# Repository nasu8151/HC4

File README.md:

¡¡¡ガバガバEnglish注意報発令中!!!

# Table of Contents
- [Table of Contents](#table-of-contents)
- [Descriptions](#descriptions)
- [Architecture](#architecture)
  - [Overview](#overview)
  - [Block diagram](#block-diagram)
  - [Instructions list](#instructions-list)
- [Software](#software)
- [List of files and folders](#list-of-files-and-folders)

# Descriptions

A 4- or 8-bit CPU made with 74-series logic ICs.

# Manuals

- Hardware manual (JP): [UsersManual_Hardware.md](./UsersManual_Hardware.md)
- Software manual (EN): [UsersManual_Software.md](./UsersManual_Software.md)
- Software manual (JP): [UsersManual_Software_JP.md](./UsersManual_Software_JP.md)

Document roles:

- Hardware manual (JP): block-level architecture, buses, control signals, model differences.
- Software manual (EN/JP): instruction set reference, programming caveats, and LED blink tutorial.

# Architecture
## Overview

HC4 has an 8-bit wide address bus and a 4-bit wide data bus.
All of instructions are 8-bit wide.

## Block diagram

## Instructions list

Please refer to [here](https://github.com/nasu8151/HC4/blob/main/UsersManual_Software.md).

## Schematics and Boards

If you don't have [KiCAD](https://www.kicad.org/), you can use KiCanvas to see our schematics and boards.
* [HC4](https://kicanvas.org/?repo=https%3A%2F%2Fgithub.com%2Fnasu8151%2FHC4%2Ftree%2Fmain%2FHC4_KiCad)
* [HC4<sub>E</sub>](https://kicanvas.org/?repo=https%3A%2F%2Fgithub.com%2Fnasu8151%2FHC4%2Ftree%2Fmain%2FHC4_KiCad_EE)

# Software

## Assembler

The assembler for this CPU can be found [here](https://github.com/nasu8151/hcxasm).
Please see the documents for syntax and other details.

## HC4eROMandRAM

This is a ROM/RAM emulator for HC4<sub>E</sub>.

# List of files and folders

<pre>
.
├─extra
├─HC4eROMandRAM
│  └─inst
├─hc4_asm
│  └─src
│      └─debug_data
├─HC4_KiCad
│  ├─HC4_gbr
│  ├─Library.pretty
│  └─sim
├─HC4_KiCad_EE
│  ├─HC4_KiCad_EE-backups
│  ├─Library.pretty
│  └─production
├─HC_MemoryBoard
│  ├─production
│  └─ThroughHole.pretty
└─verilog
    ├─HC4
    ├─HC4e
    └─HC8
</pre>

* [README.md](https://github.com/nasu8151/HC4) : This file.
* [UsersManual_Software.md](https://github.com/nasu8151/HC4/blob/main/UsersManual_Software.md) : Instruction manual.
* [hc4_asm/](https://github.com/nasu8151/HC4/blob/main/hc4_asm) : [DEPRECATED] : [Use new assembler](https://github.com/nasu8151/hcxasm). An assembler for the HC4 CPU.
* [HC4_KiCad](https://github.com/nasu8151/HC4/blob/main/HC4_KiCad) : Schematics and a board of the HC4.
* [HC4_KiCad_EE](https://github.com/nasu8151/HC4/blob/main/HC4_KiCad_EE) : Schematics and a board of the HC4<sub>E</sub> (Used to be called "HC4 Education Edition").
* [HC_MemoryBoard](https://github.com/nasu8151/HC4/blob/main/HC4_KiCad_EE) : A schematic and a board for SRAM and I/O.
* verilog/
  * [verilog/HC4](https://github.com/nasu8151/HC4/blob/main/verilog/HC4) : Verilog simulation files of the HC4 CPU.
  * [verilog/HC8](https://github.com/nasu8151/blob/main/HC4/verilog/HC8) : Verilog simulation files of the HC8 CPU.
  * [verilog/HC4e](https://github.com/nasu8151/blob/main/HC4/verilog/HC8) : Verilog simulation files of the HC4e CPU.

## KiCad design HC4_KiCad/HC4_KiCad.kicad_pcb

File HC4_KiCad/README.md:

Schematics and board of HC4.

BOM:
[Bill of materials](https://github.com/nasu8151/HC4/blob/main/HC4_KiCad/BOM_HC4.md)

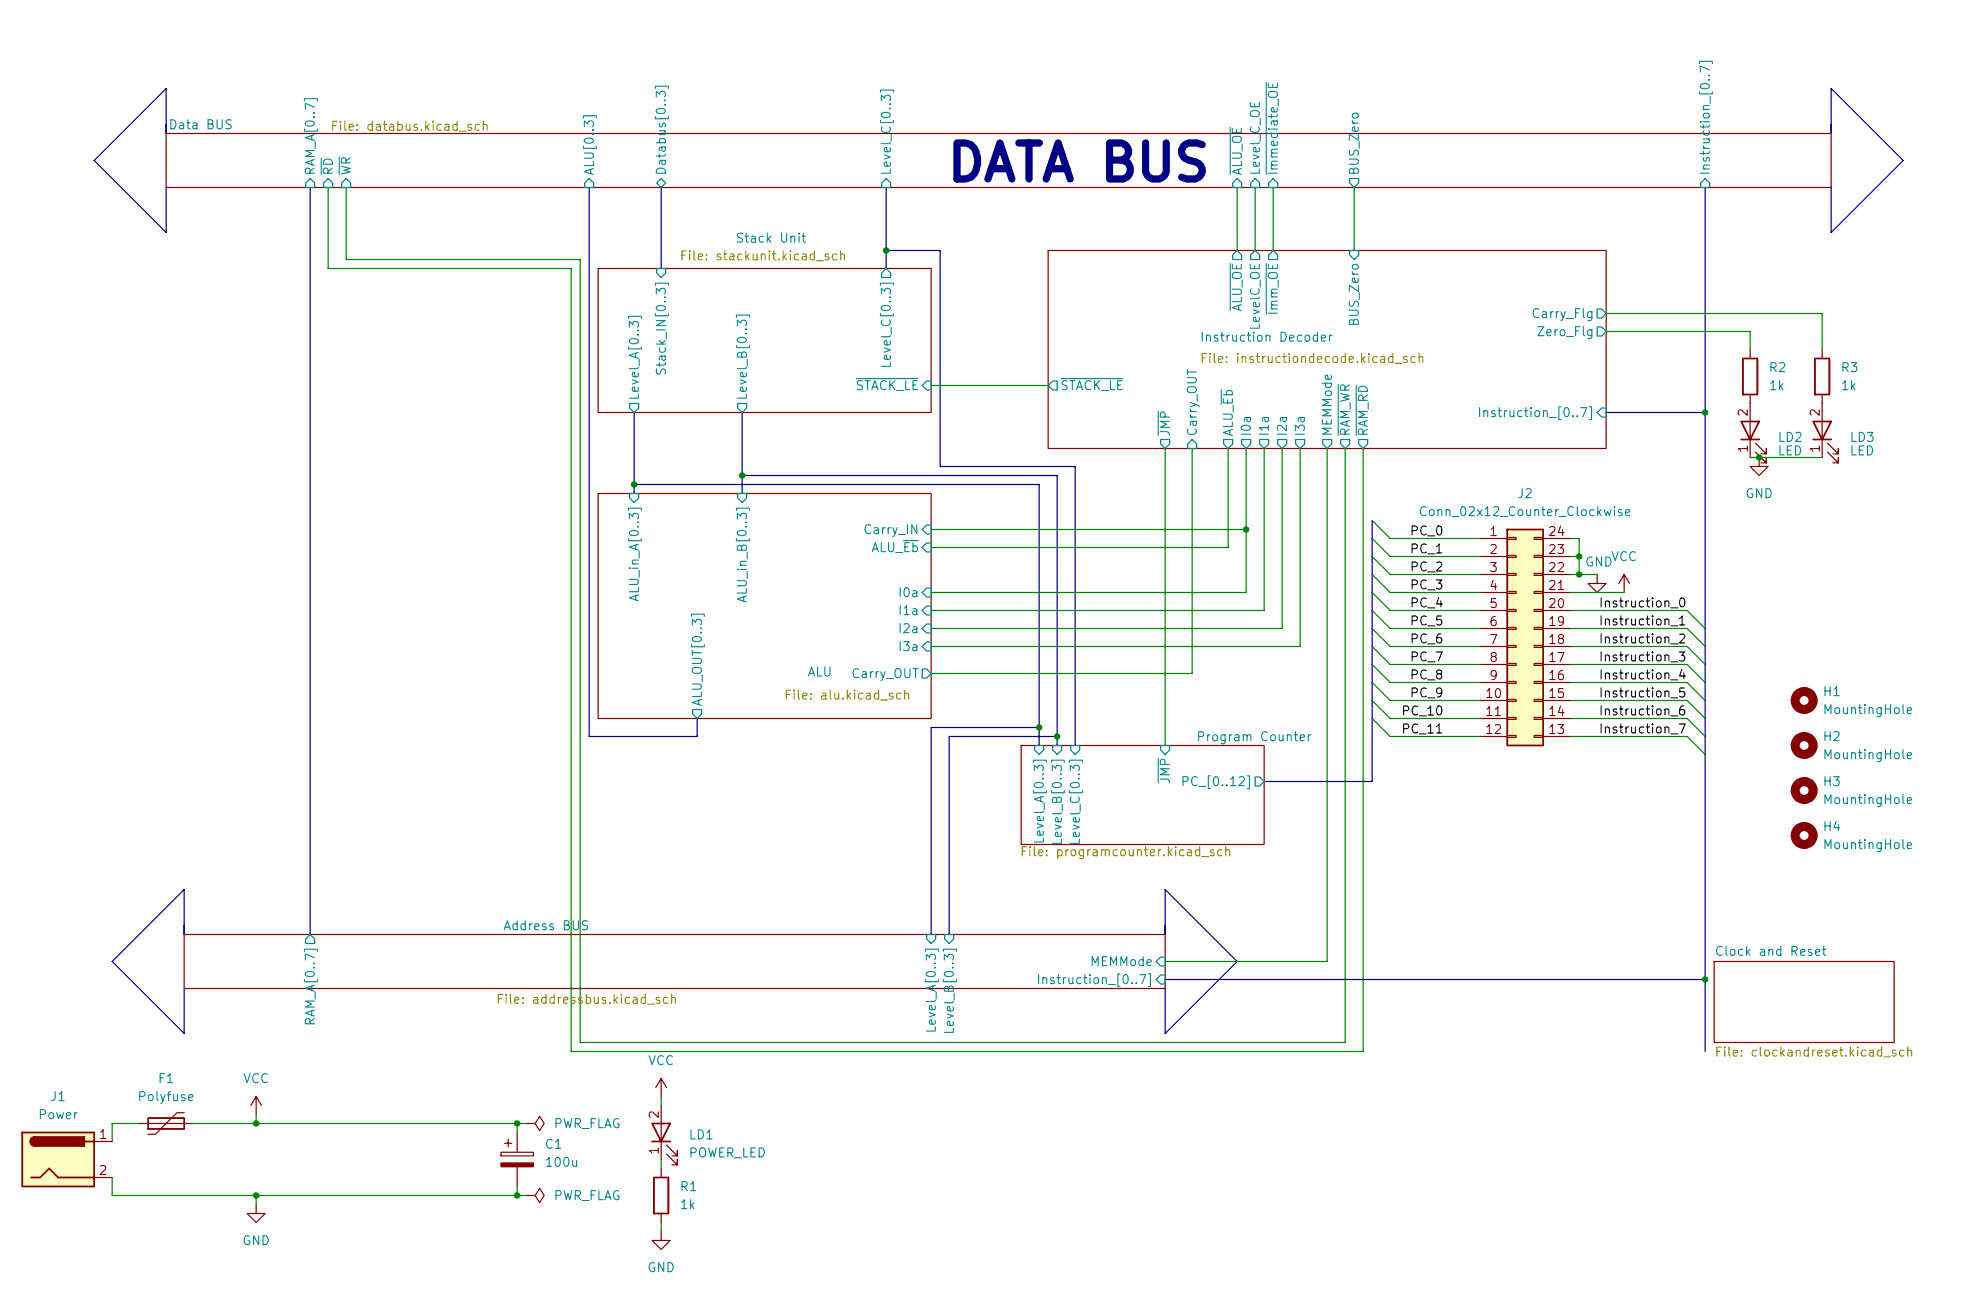
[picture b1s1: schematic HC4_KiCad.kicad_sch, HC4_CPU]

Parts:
C1: 100u; CP_Radial_D5.0mm_P2.50mm
F1: Polyfuse; Fuse_Bourns_MF-RG400
H1, H2, H3, H4: MountingHole; MountingHole_3.2mm_M3
J1: Power; BarrelJack_GCT_DCJ200-10-A_Horizontal
J2: Conn_02x12_Counter_Clockwise; PinHeader_2x12_P2.54mm_Vertical
LD1: POWER_LED; LED_Rectangular_W5.0mm_H2.0mm
LD2, LD3: LED; LED_Rectangular_W5.0mm_H2.0mm
R1, R2, R3: 1k; R_0603_1608Metric

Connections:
/Address BUS/Instruction_0: J2.20; also elsewhere on the board
/Address BUS/Instruction_1: J2.19; also elsewhere on the board
/Address BUS/Instruction_2: J2.18; also elsewhere on the board
/Address BUS/Instruction_3: J2.17; also elsewhere on the board
/Address BUS/Instruction_4: J2.16; also elsewhere on the board
/Address BUS/Instruction_5: J2.15; also elsewhere on the board
/Address BUS/Instruction_6: J2.14; also elsewhere on the board
/Address BUS/Instruction_7: J2.13; also elsewhere on the board
/Instruction Decoder/Carry_Flg: R3.1; also elsewhere on the board
/Instruction Decoder/Zero_Flg: R2.1; also elsewhere on the board
/Program Counter/PC_0: J2.1; also elsewhere on the board
/Program Counter/PC_1: J2.2; also elsewhere on the board
/Program Counter/PC_2: J2.3; also elsewhere on the board
/Program Counter/PC_3: J2.4; also elsewhere on the board
/Program Counter/PC_4: J2.5; also elsewhere on the board
/Program Counter/PC_5: J2.6; also elsewhere on the board
/Program Counter/PC_6: J2.7; also elsewhere on the board
/Program Counter/PC_7: J2.8; also elsewhere on the board
/Program Counter/PC_8: J2.9; also elsewhere on the board
/Program Counter/PC_9: J2.10; also elsewhere on the board
/Program Counter/PC_10: J2.11; also elsewhere on the board
/Program Counter/PC_11: J2.12; also elsewhere on the board
GND: C1.2, J1.2, J2.22, J2.23, J2.24, LD2.1 (K_1), LD3.1 (K_1), R1.2; also elsewhere on the board
unnamed: F1.1, J1.1
unnamed: LD1.1 (K_1), R1.1
unnamed: LD2.2, R2.2
unnamed: LD3.2, R3.2
VCC: C1.1, F1.2, J2.21, LD1.2; also elsewhere on the board

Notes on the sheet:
DATA BUS

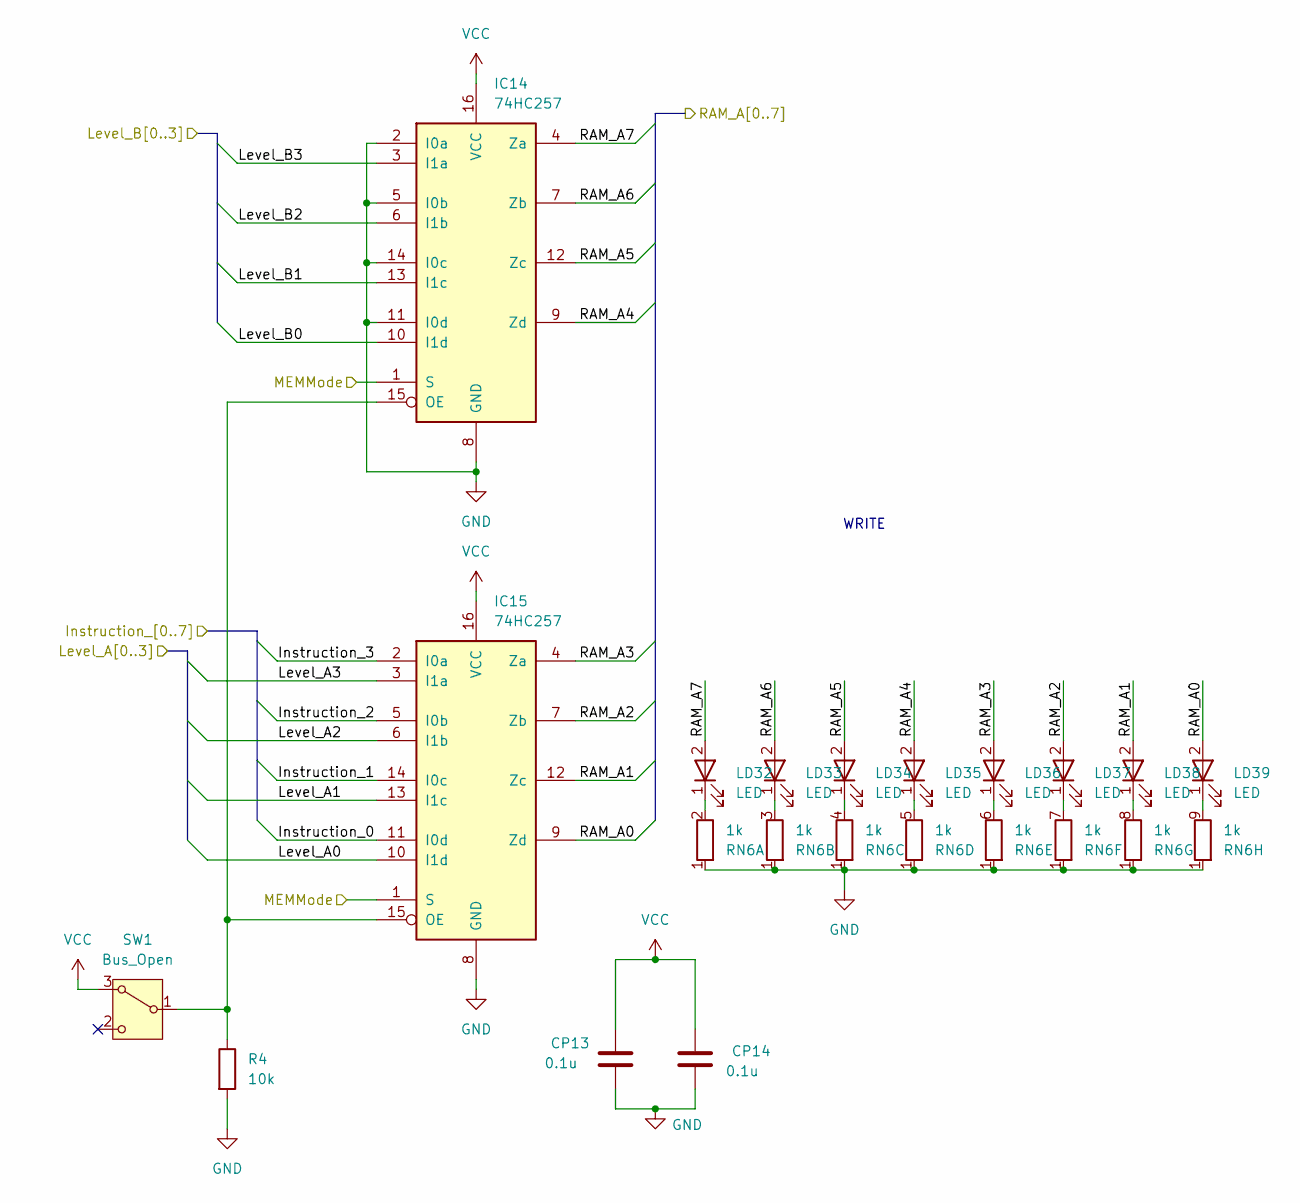
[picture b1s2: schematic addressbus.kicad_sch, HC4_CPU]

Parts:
CP13, CP14: 0.1u; C_0603_1608Metric
IC14, IC15: 74HC257; DIP-16_W7.62mm
LD32, LD33, LD34, LD35, LD36, LD37, LD38, LD39: LED; LED_Rectangular_W5.0mm_H2.0mm
R4: 10k; R_0603_1608Metric
RN6: 1k; R_Array_SIP9
SW1: Bus_Open; SW_Slide-03_Wuerth-WS-SLTV_10x2.5x6.4_P2.54mm

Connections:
/ALU/ALU_in_A0: IC15.10 (I1d); also elsewhere on the board
/ALU/ALU_in_A1: IC15.13 (I1c); also elsewhere on the board
/ALU/ALU_in_A2: IC15.6 (I1b); also elsewhere on the board
/ALU/ALU_in_A3: IC15.3 (I1a); also elsewhere on the board
/ALU/ALU_in_B0: IC14.10 (I1d); also elsewhere on the board
/ALU/ALU_in_B1: IC14.13 (I1c); also elsewhere on the board
/ALU/ALU_in_B2: IC14.6 (I1b); also elsewhere on the board
/ALU/ALU_in_B3: IC14.3 (I1a); also elsewhere on the board
/Address BUS/Instruction_0: IC15.11 (I0d); also elsewhere on the board
/Address BUS/Instruction_1: IC15.14 (I0c); also elsewhere on the board
/Address BUS/Instruction_2: IC15.5 (I0b); also elsewhere on the board
/Address BUS/Instruction_3: IC15.2 (I0a); also elsewhere on the board
/Address BUS/MEMMode: IC14.1 (S), IC15.1 (S); also elsewhere on the board
/Address BUS/RAM_A0: IC15.9 (Zd), LD39.2; also elsewhere on the board
/Address BUS/RAM_A1: IC15.12 (Zc), LD38.2; also elsewhere on the board
/Address BUS/RAM_A2: IC15.7 (Zb), LD37.2; also elsewhere on the board
/Address BUS/RAM_A3: IC15.4 (Za), LD36.2; also elsewhere on the board
/Address BUS/RAM_A4: IC14.9 (Zd), LD35.2; also elsewhere on the board
/Address BUS/RAM_A5: IC14.12 (Zc), LD34.2; also elsewhere on the board
/Address BUS/RAM_A6: IC14.7 (Zb), LD33.2; also elsewhere on the board
/Address BUS/RAM_A7: IC14.4 (Za), LD32.2; also elsewhere on the board
GND: CP13.2, CP14.2, IC14.2 (I0a), IC14.5 (I0b), IC14.8 (GND), IC14.11 (I0d), IC14.14 (I0c), IC15.8 (GND), R4.2, RN6.1 (R1); also elsewhere on the board
unnamed: IC14.15 (OE), IC15.15 (OE), R4.1, SW1.1 (B)
unnamed: LD32.1 (K_1), RN6.2 (R1.2)
unnamed: LD33.1 (K_1), RN6.3 (R2.2)
unnamed: LD34.1 (K_1), RN6.4 (R3.2)
unnamed: LD35.1 (K_1), RN6.5 (R4.2)
unnamed: LD36.1 (K_1), RN6.6 (R5.2)
unnamed: LD37.1 (K_1), RN6.7 (R6.2)
unnamed: LD38.1 (K_1), RN6.8 (R7.2)
unnamed: LD39.1 (K_1), RN6.9 (R8.2)
VCC: CP13.1, CP14.1, IC14.16 (VCC), IC15.16 (VCC), SW1.3 (A); also elsewhere on the board

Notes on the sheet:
WRITE

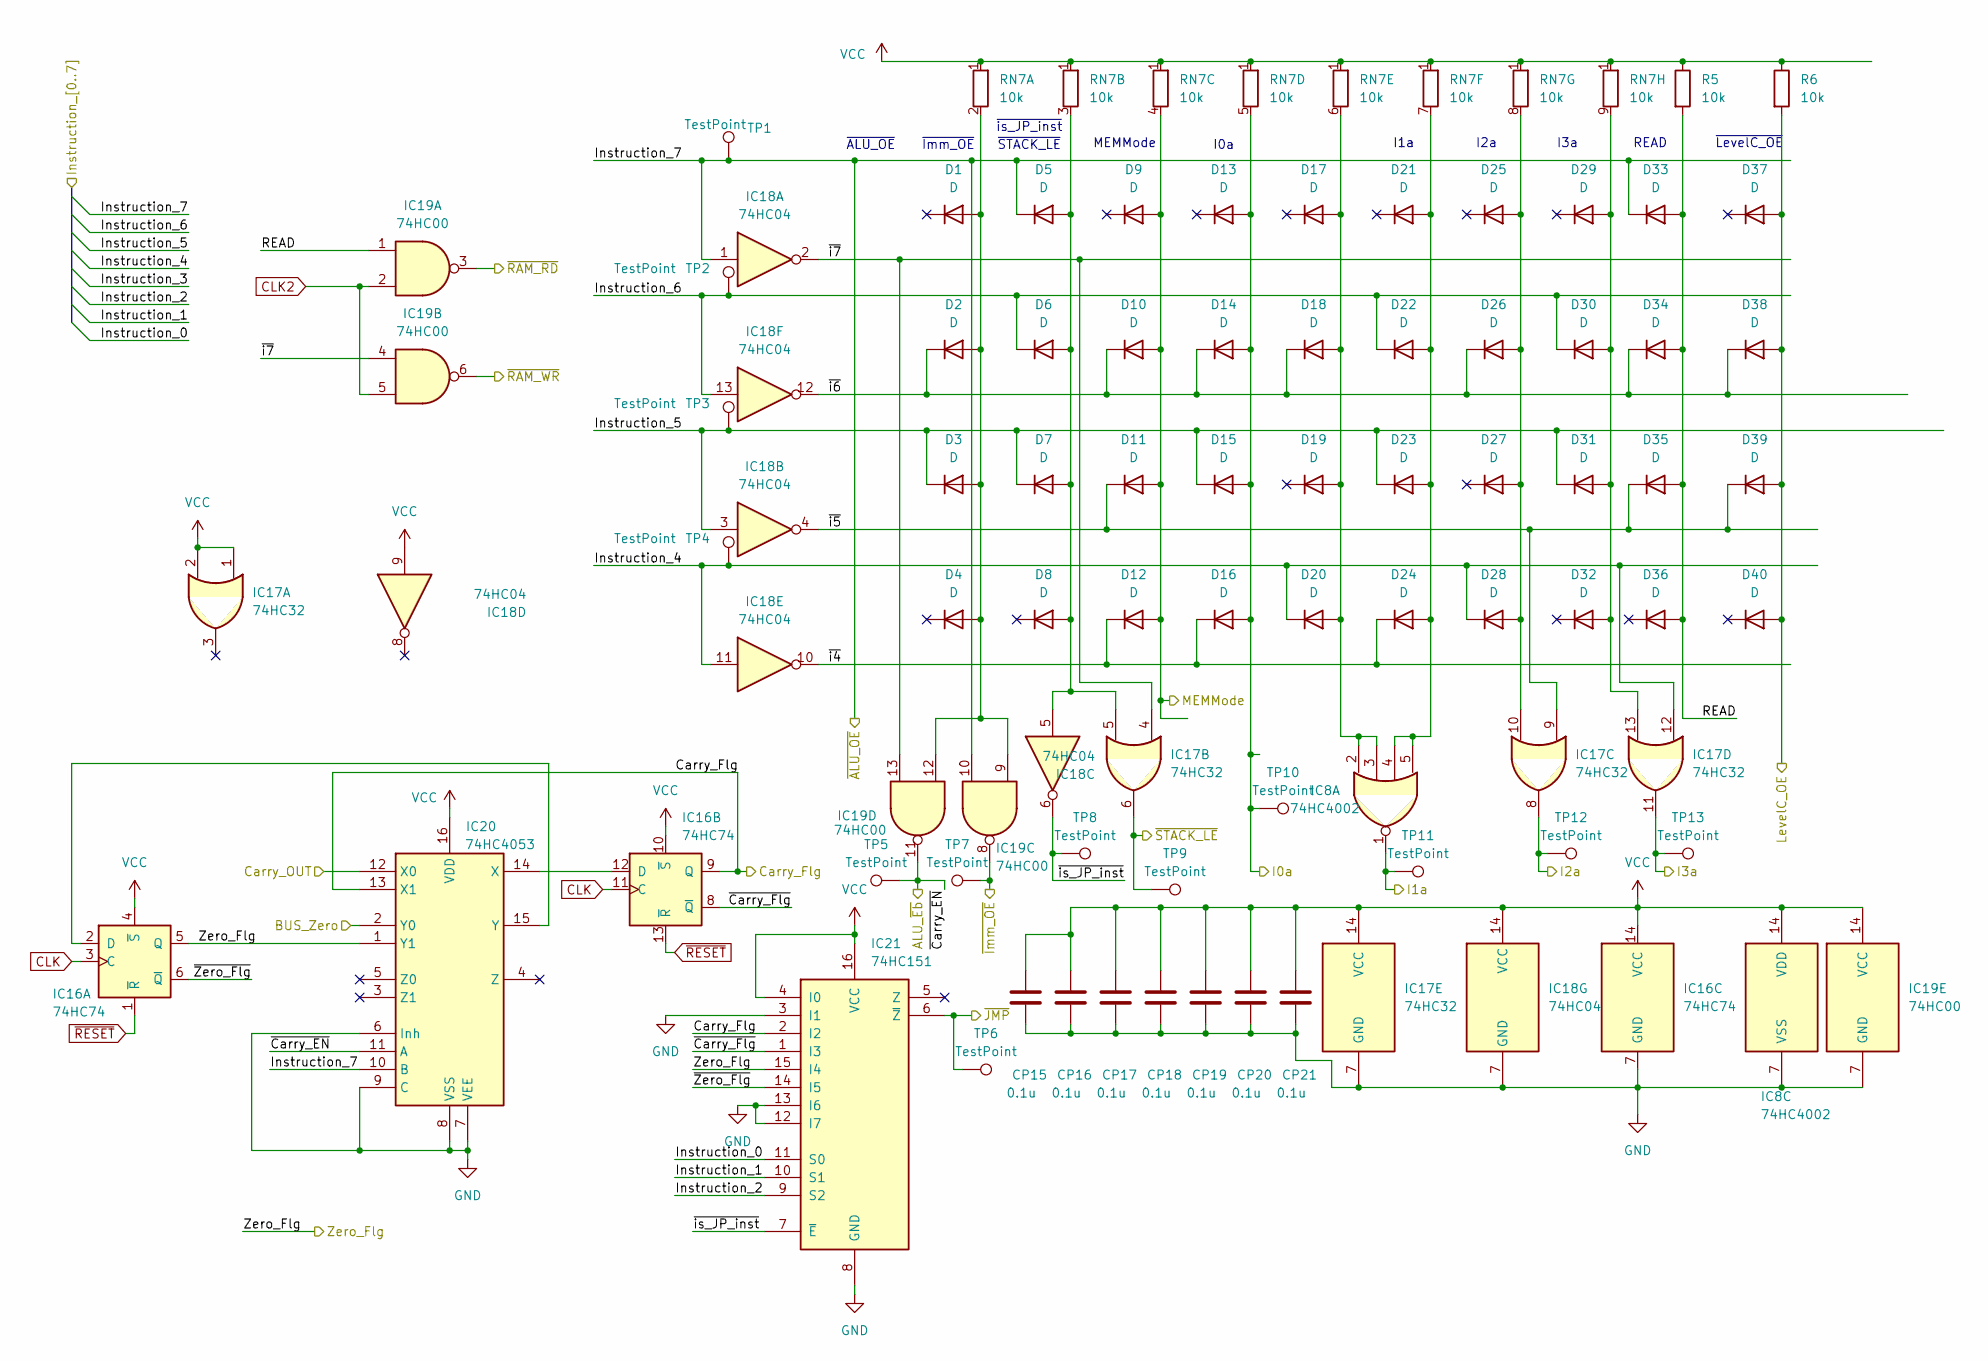
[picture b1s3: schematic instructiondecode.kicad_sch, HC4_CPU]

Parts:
CP15, CP16, CP17, CP18, CP19, CP20, CP21: 0.1u; C_0603_1608Metric
D1, D2, D3, D4, D5, D6, D7, D8, D9, D10, D11, D12, D13, D14, D15, D16, D17, D18, D19, D20, D21, D22, D23, D24, D25, D26, D27, D28, D29, D30, D31, D32, D33, D34, D35, D36, D37, D38, D39, D40: D; D_SOD-323_HandSoldering
IC8: 74HC4002; DIP-14_W7.62mm
IC16: 74HC74; DIP-14_W7.62mm
IC17: 74HC32; DIP-14_W7.62mm
IC18: 74HC04; DIP-14_W7.62mm
IC19: 74HC00; DIP-14_W7.62mm
IC20: 74HC4053; DIP-16_W7.62mm
IC21: 74HC151; DIP-16_W7.62mm
R5, R6: 10k; R_0603_1608Metric
RN7: 10k; R_Array_SIP9
TP1, TP2, TP3, TP4, TP5, TP6, TP7, TP8, TP9, TP10, TP11, TP12, TP13: TestPoint; TestPoint_THTPad_1.0x1.0mm_Drill0.5mm

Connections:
/ALU/Carry_IN: D13.2 (A_2), D14.2 (A), D15.2 (A), D16.2 (A), RN7.5 (R4.2), TP10.1 (1_1); also elsewhere on the board
/ALU/Carry_OUT: IC20.12 (X0); also elsewhere on the board
/ALU/I1a: IC8.1, TP11.1 (1_1); also elsewhere on the board
/ALU/I2a: IC17.8, TP12.1 (1_1); also elsewhere on the board
/ALU/I3a: IC17.11, TP13.1 (1_1); also elsewhere on the board
/Address BUS/Instruction_0: IC21.11 (S0); also elsewhere on the board
/Address BUS/Instruction_1: IC21.10 (S1); also elsewhere on the board
/Address BUS/Instruction_2: IC21.9 (S2); also elsewhere on the board
/Address BUS/Instruction_4: D20.1 (K), D28.1 (K), IC17.12, IC18.11, TP4.1 (1_1); also elsewhere on the board
/Address BUS/Instruction_5: D3.1 (K), D7.1 (K), D15.1 (K), D23.1 (K), D31.1 (K), IC18.3, TP3.1 (1_1); also elsewhere on the board
/Address BUS/Instruction_6: D6.1 (K), D22.1 (K), D30.1 (K), IC18.13, TP2.1 (1_1); also elsewhere on the board
/Address BUS/Instruction_7: D5.1 (K), D33.1 (K), IC18.1, IC19.10, IC20.10 (B), TP1.1 (1_1); also elsewhere on the board
/Address BUS/MEMMode: D9.2 (A_2), D10.2 (A), D11.2 (A), D12.2 (A), RN7.4 (R3.2); also elsewhere on the board
/Data BUS/BUS_Zero: IC20.2 (Y0); also elsewhere on the board
/Data BUS/Level_C_OE: D37.2 (A_2), D38.2 (A), D39.2 (A), D40.2 (A_2), R6.2; also elsewhere on the board
/Data BUS/~Immediate_OE: IC19.8, TP7.1 (1_1); also elsewhere on the board
/Data BUS/~RD: IC19.3; also elsewhere on the board
/Data BUS/~WR: IC19.6; also elsewhere on the board
/Instruction Decoder/Carry_Flg: IC16.9 (Q), IC20.13 (X1), IC21.2 (I2); also elsewhere on the board
/Instruction Decoder/READ: D33.2 (A), D34.2 (A), D35.2 (A), D36.2 (A_2), IC19.1, R5.2
/Instruction Decoder/Zero_Flg: IC16.5 (Q), IC20.1 (Y1), IC21.15 (I4); also elsewhere on the board
/Instruction Decoder/~Carry_EN: IC19.11, IC20.11 (A), TP5.1 (1_1); also elsewhere on the board
/Instruction Decoder/~Carry_Flg: IC16.8 (~Q), IC21.1 (I3)
/Instruction Decoder/~JMP: IC21.6 (~Z), TP6.1 (1_1); also elsewhere on the board
/Instruction Decoder/~STACK_LE: IC17.6, TP9.1 (1_1); also elsewhere on the board
/Instruction Decoder/~Zero_Flg: IC16.6 (~Q), IC21.14 (I5)
/Instruction Decoder/~i4: D12.1 (K), D16.1 (K), D24.1 (K), IC18.10
/Instruction Decoder/~i5: D11.1 (K), D35.1 (K), D39.1 (K), IC17.9, IC18.4
/Instruction Decoder/~i6: D2.1 (K), D10.1 (K), D14.1 (K), D18.1 (K), D26.1 (K), D34.1 (K), D38.1 (K), IC18.12
/Instruction Decoder/~i7: IC17.4, IC18.2, IC19.4, IC19.13
/Instruction Decoder/~is_JP_inst: IC18.6, IC21.7 (~E), TP8.1 (1_1)
CLK: IC16.3 (C), IC16.11 (C); also elsewhere on the board
CLK2: IC19.2, IC19.5; also elsewhere on the board
GND: CP15.2, CP16.2, CP17.2, CP18.2, CP19.2, CP20.2, CP21.2, IC8.7 (VSS), IC16.7 (GND), IC17.7 (GND), IC18.7 (GND), IC19.7 (GND), IC20.6 (Inh), IC20.7 (VEE), IC20.8 (VSS), IC20.9 (C), IC21.3 (I1), IC21.8 (GND), IC21.12 (I7), IC21.13 (I6); also elsewhere on the board
unnamed: D1.2 (A_2), D2.2 (A), D3.2 (A), D4.2 (A_2), IC19.9, IC19.12, RN7.2 (R1.2)
unnamed: D5.2 (A), D6.2 (A), D7.2 (A), D8.2 (A_2), IC17.5, IC18.5, RN7.3 (R2.2)
unnamed: D17.2 (A_2), D18.2 (A), D19.2 (A_2), D20.2 (A), IC8.2, IC8.3, RN7.6 (R5.2)
unnamed: D21.2 (A_2), D22.2 (A), D23.2 (A), D24.2 (A), IC8.4, IC8.5, RN7.7 (R6.2)
unnamed: D25.2 (A_2), D26.2 (A), D27.2 (A_2), D28.2 (A), IC17.10, RN7.8 (R7.2)
unnamed: D29.2 (A_2), D30.2 (A), D31.2 (A), D32.2 (A_2), IC17.13, RN7.9 (R8.2)
unnamed: IC16.2 (D), IC20.15 (Y)
unnamed: IC16.12 (D), IC20.14 (X)
VCC: CP15.1, CP16.1, CP17.1, CP18.1, CP19.1, CP20.1, CP21.1, IC8.14 (VDD), IC16.4 (~S), IC16.10 (~S), IC16.14 (VCC), IC17.1, IC17.2, IC17.14 (VCC), IC18.9, IC18.14 (VCC), IC19.14 (VCC), IC20.16 (VDD), IC21.4 (I0), IC21.16 (VCC), R5.1, R6.1, RN7.1 (R1); also elsewhere on the board
~RESET: IC16.1 (~R), IC16.13 (~R); also elsewhere on the board

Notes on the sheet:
I2a
I0a
~{Imm_OE}
~{LevelC_OE}
~{ALU_OE}
~{STACK_LE}
I3a
READ
MEMMode
I1a
~{is_JP_inst}

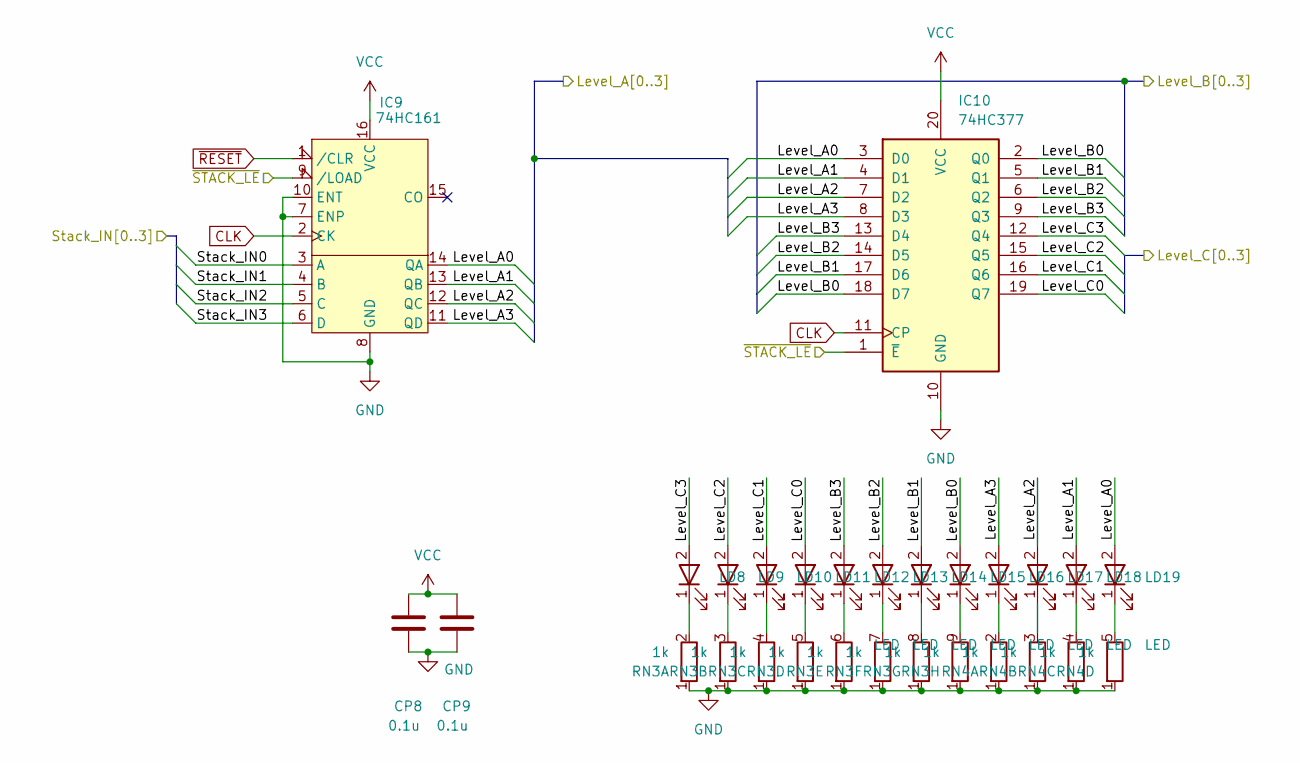
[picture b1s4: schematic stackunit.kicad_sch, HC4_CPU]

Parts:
CP8, CP9: 0.1u; C_0603_1608Metric
IC9: 74HC161; DIP-16_W7.62mm
IC10: 74HC377; DIP-20_W7.62mm
LD8, LD9, LD10, LD11, LD12, LD13, LD14, LD15, LD16, LD17, LD18, LD19: LED; LED_Rectangular_W5.0mm_H2.0mm
RN3, RN4: 1k; R_Array_SIP9

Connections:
/ALU/ALU_in_A0: IC9.14 (QA), IC10.3 (D0), LD19.2; also elsewhere on the board
/ALU/ALU_in_A1: IC9.13 (QB), IC10.4 (D1), LD18.2; also elsewhere on the board
/ALU/ALU_in_A2: IC9.12 (QC), IC10.7 (D2), LD17.2; also elsewhere on the board
/ALU/ALU_in_A3: IC9.11 (QD), IC10.8 (D3), LD16.2; also elsewhere on the board
/ALU/ALU_in_B0: IC10.2 (Q0), IC10.18 (D7), LD15.2; also elsewhere on the board
/ALU/ALU_in_B1: IC10.5 (Q1), IC10.17 (D6), LD14.2; also elsewhere on the board
/ALU/ALU_in_B2: IC10.6 (Q2), IC10.14 (D5), LD13.2; also elsewhere on the board
/ALU/ALU_in_B3: IC10.9 (Q3), IC10.13 (D4), LD12.2; also elsewhere on the board
/Data BUS/Databus0: IC9.3 (A); also elsewhere on the board
/Data BUS/Databus1: IC9.4 (B); also elsewhere on the board
/Data BUS/Databus2: IC9.5 (C); also elsewhere on the board
/Data BUS/Databus3: IC9.6 (D); also elsewhere on the board
/Data BUS/Level_C0: IC10.19 (Q7), LD11.2; also elsewhere on the board
/Data BUS/Level_C1: IC10.16 (Q6), LD10.2; also elsewhere on the board
/Data BUS/Level_C2: IC10.15 (Q5), LD9.2; also elsewhere on the board
/Data BUS/Level_C3: IC10.12 (Q4), LD8.2; also elsewhere on the board
/Instruction Decoder/~STACK_LE: IC9.9 (/LOAD), IC10.1 (~E); also elsewhere on the board
CLK: IC9.2 (CK), IC10.11 (CP); also elsewhere on the board
GND: CP8.2, CP9.2, IC9.7 (ENP), IC9.8 (GND), IC9.10 (ENT), IC10.10 (GND), RN3.1 (R1), RN4.1 (R1); also elsewhere on the board
unnamed: LD8.1 (K_1), RN3.2 (R1.2)
unnamed: LD9.1 (K_1), RN3.3 (R2.2)
unnamed: LD10.1 (K_1), RN3.4 (R3.2)
unnamed: LD11.1 (K_1), RN3.5 (R4.2)
unnamed: LD12.1 (K_1), RN3.6 (R5.2)
unnamed: LD13.1 (K_1), RN3.7 (R6.2)
unnamed: LD14.1 (K_1), RN3.8 (R7.2)
unnamed: LD15.1 (K_1), RN3.9 (R8.2)
unnamed: LD16.1 (K_1), RN4.2 (R1.2)
unnamed: LD17.1 (K_1), RN4.3 (R2.2)
unnamed: LD18.1 (K_1), RN4.4 (R3.2)
unnamed: LD19.1 (K_1), RN4.5 (R4.2)
VCC: CP8.1, CP9.1, IC9.16 (VCC), IC10.20 (VCC); also elsewhere on the board
~RESET: IC9.1 (/CLR); also elsewhere on the board

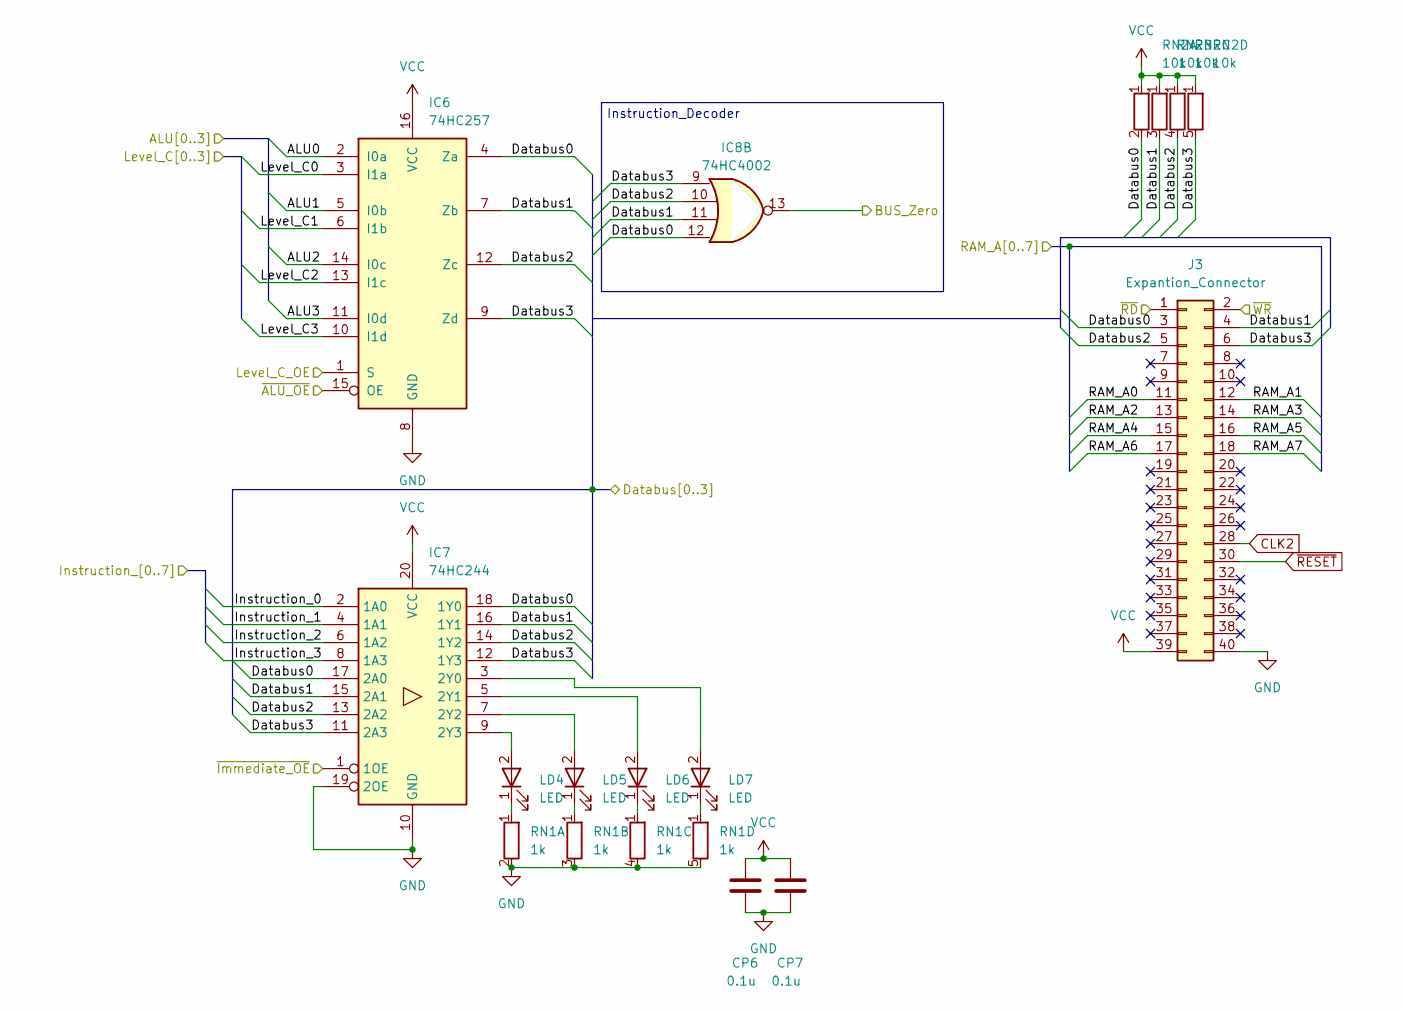
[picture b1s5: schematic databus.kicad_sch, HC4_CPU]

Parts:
CP6, CP7: 0.1u; C_0603_1608Metric
IC6: 74HC257; DIP-16_W7.62mm
IC7: 74HC244; DIP-20_W7.62mm
IC8: 74HC4002; DIP-14_W7.62mm
J3: Expantion_Connector; PinHeader_2x20_P2.54mm_Vertical
LD4, LD5, LD6, LD7: LED; LED_Rectangular_W5.0mm_H2.0mm
RN1: 1k; R_Array_SIP5
RN2: 10k; R_Array_SIP5

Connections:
/ALU/ALU_OUT0: IC6.2 (I0a); also elsewhere on the board
/ALU/ALU_OUT1: IC6.5 (I0b); also elsewhere on the board
/ALU/ALU_OUT2: IC6.14 (I0c); also elsewhere on the board
/ALU/ALU_OUT3: IC6.11 (I0d); also elsewhere on the board
/Address BUS/Instruction_0: IC7.2 (1A0); also elsewhere on the board
/Address BUS/Instruction_1: IC7.4 (1A1); also elsewhere on the board
/Address BUS/Instruction_2: IC7.6 (1A2); also elsewhere on the board
/Address BUS/Instruction_3: IC7.8 (1A3); also elsewhere on the board
/Address BUS/Instruction_7: IC6.15 (OE); also elsewhere on the board
/Address BUS/RAM_A0: J3.11; also elsewhere on the board
/Address BUS/RAM_A1: J3.12; also elsewhere on the board
/Address BUS/RAM_A2: J3.13; also elsewhere on the board
/Address BUS/RAM_A3: J3.14; also elsewhere on the board
/Address BUS/RAM_A4: J3.15; also elsewhere on the board
/Address BUS/RAM_A5: J3.16; also elsewhere on the board
/Address BUS/RAM_A6: J3.17; also elsewhere on the board
/Address BUS/RAM_A7: J3.18; also elsewhere on the board
/Data BUS/BUS_Zero: IC8.13; also elsewhere on the board
/Data BUS/Databus0: IC6.4 (Za), IC7.17 (2A0), IC7.18 (1Y0), IC8.12, J3.3, RN2.2 (R1.2); also elsewhere on the board
/Data BUS/Databus1: IC6.7 (Zb), IC7.15 (2A1), IC7.16 (1Y1), IC8.11, J3.4, RN2.3 (R2.2); also elsewhere on the board
/Data BUS/Databus2: IC6.12 (Zc), IC7.13 (2A2), IC7.14 (1Y2), IC8.10, J3.5, RN2.4 (R3.2); also elsewhere on the board
/Data BUS/Databus3: IC6.9 (Zd), IC7.11 (2A3), IC7.12 (1Y3), IC8.9, J3.6, RN2.5 (R4.2); also elsewhere on the board
/Data BUS/Level_C0: IC6.3 (I1a); also elsewhere on the board
/Data BUS/Level_C1: IC6.6 (I1b); also elsewhere on the board
/Data BUS/Level_C2: IC6.13 (I1c); also elsewhere on the board
/Data BUS/Level_C3: IC6.10 (I1d); also elsewhere on the board
/Data BUS/Level_C_OE: IC6.1 (S); also elsewhere on the board
/Data BUS/~Immediate_OE: IC7.1 (1OE); also elsewhere on the board
/Data BUS/~RD: J3.1; also elsewhere on the board
/Data BUS/~WR: J3.2; also elsewhere on the board
CLK2: J3.28; also elsewhere on the board
GND: CP6.2, CP7.2, IC6.8 (GND), IC7.10 (GND), IC7.19 (2OE), J3.40, RN1.2 (R1.2), RN1.3 (R2.2), RN1.4 (R3.2), RN1.5 (R4.2); also elsewhere on the board
unnamed: IC7.3 (2Y0), LD7.2
unnamed: IC7.5 (2Y1), LD6.2
unnamed: IC7.7 (2Y2), LD5.2
unnamed: IC7.9 (2Y3), LD4.2
VCC: CP6.1, CP7.1, IC6.16 (VCC), IC7.20 (VCC), J3.39, RN2.1 (R1); also elsewhere on the board
~RESET: J3.30; also elsewhere on the board

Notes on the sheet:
Instruction_Decoder

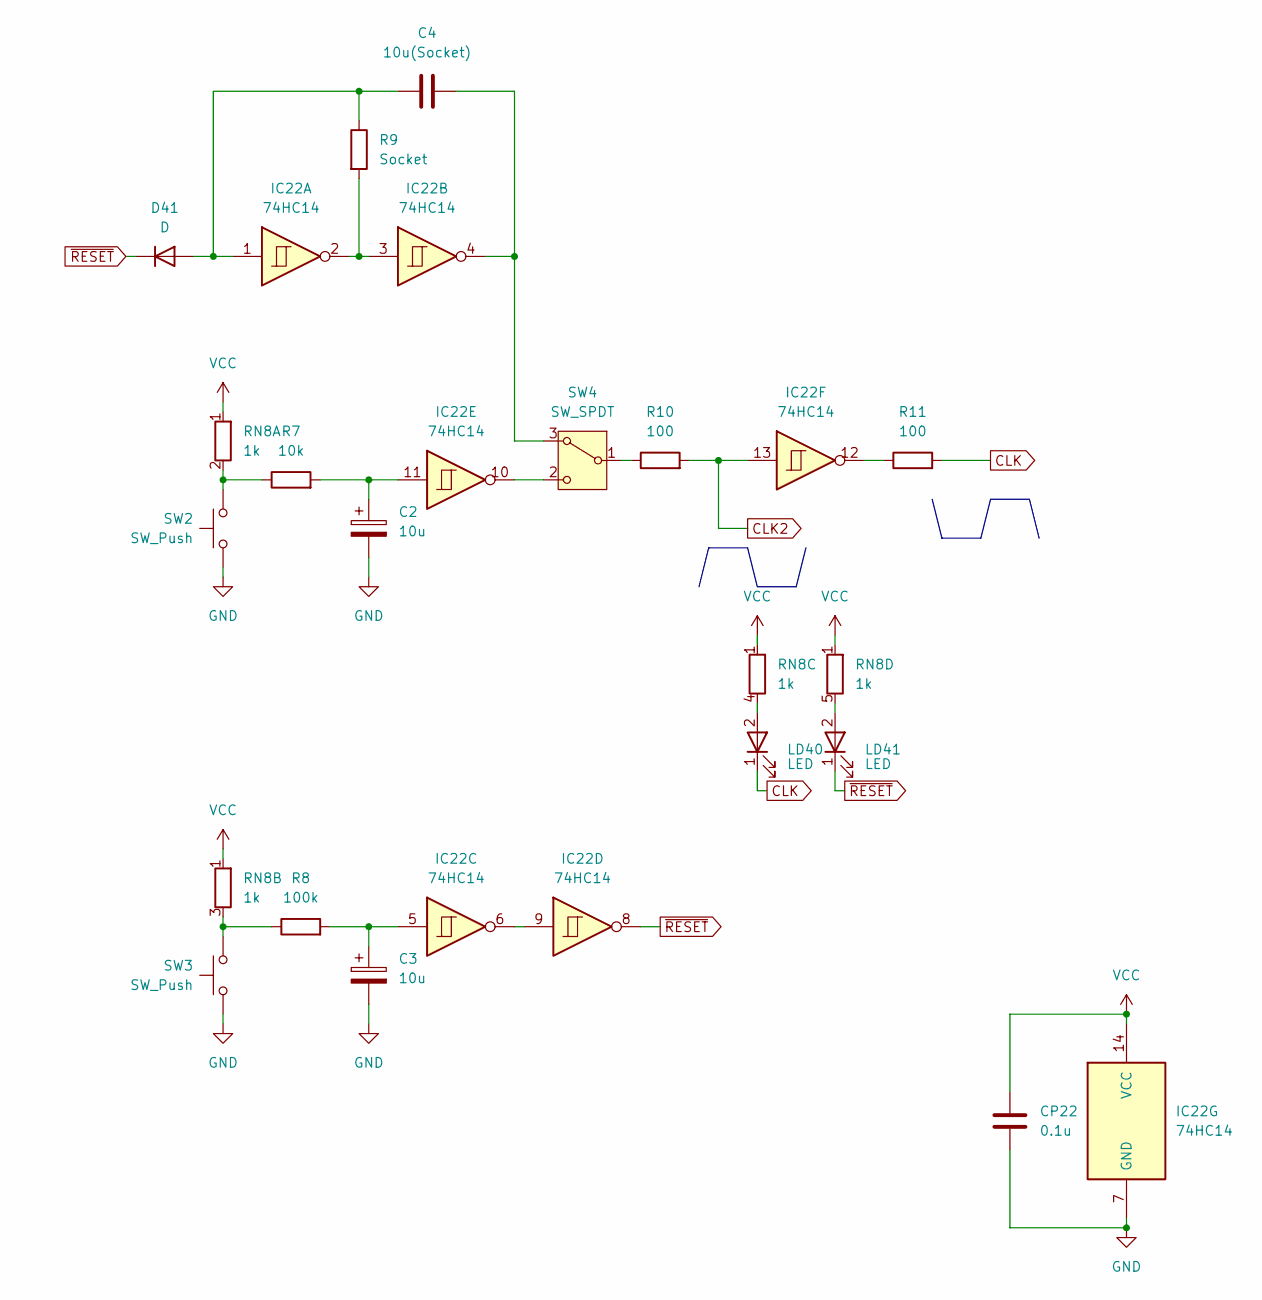
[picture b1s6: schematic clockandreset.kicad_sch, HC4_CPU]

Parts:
C2, C3: 10u; CP_Radial_D5.0mm_P2.50mm
C4: 10u(Socket); C_Radial_D6.3mm_H5.0mm_P2.50mm
CP22: 0.1u; C_0603_1608Metric
D41: D; D_SOD-323_HandSoldering
IC22: 74HC14; DIP-14_W7.62mm
LD40, LD41: LED; LED_Rectangular_W5.0mm_H2.0mm
R7: 10k; R_0603_1608Metric
R8: 100k; R_0603_1608Metric
R9: Socket; R_Axial_DIN0207_L6.3mm_D2.5mm_P10.16mm_Horizontal
R10, R11: 100; R_0603_1608Metric
RN8: 1k; R_Array_SIP5
SW2, SW3: SW_Push; SW_PUSH_6mm
SW4: SW_SPDT; SW_Slide-03_Wuerth-WS-SLTV_10x2.5x6.4_P2.54mm

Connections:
CLK: LD40.1 (K_1), R11.2; also elsewhere on the board
CLK2: IC22.13, R10.2; also elsewhere on the board
GND: C2.2, C3.2, CP22.2, IC22.7 (GND), SW2.1, SW3.1; also elsewhere on the board
unnamed: C2.1, IC22.11, R7.2
unnamed: C3.1, IC22.5, R8.2
unnamed: C4.1, D41.2 (A), IC22.1, R9.1
unnamed: IC22.2, IC22.3, R9.2
unnamed: IC22.6, IC22.9
unnamed: IC22.12, R11.1
unnamed: R7.1, RN8.2 (R1.2), SW2.2
unnamed: R8.1, RN8.3 (R2.2), SW3.2
unnamed: LD40.2, RN8.4 (R3.2)
unnamed: LD41.2, RN8.5 (R4.2)
unnamed: C4.2, IC22.4, SW4.3 (A)
unnamed: R10.1, SW4.1 (B)
unnamed: IC22.10, SW4.2 (C)
VCC: CP22.1, IC22.14 (VCC), RN8.1 (R1); also elsewhere on the board
~RESET: D41.1 (K), IC22.8, LD41.1 (K_1); also elsewhere on the board

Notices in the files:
HC4_KiCad/HC4_KiCad.kicad_pcb:
(C)2025-26
